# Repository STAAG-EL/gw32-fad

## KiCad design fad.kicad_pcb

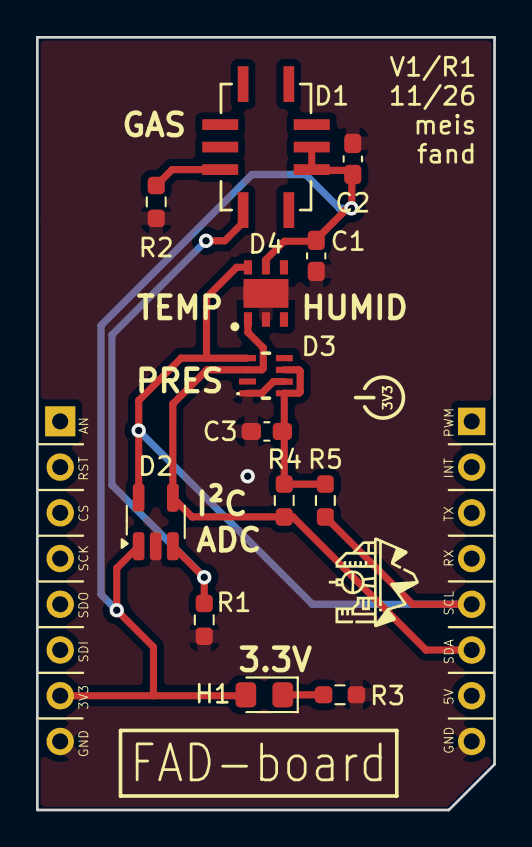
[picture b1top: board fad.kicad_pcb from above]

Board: 2 copper layers, 25.4 x 42.9 mm, 14 parts (0 on the bottom side), 7 nets.

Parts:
C1, C2, C3: 100n; C_0603_1608Metric_Pad1.08x0.95mm_HandSolder
D1: MICS-5524; MICS-SMD10
D2: MCP3221; SOT-23-5_HandSoldering
D3: DPS368
D4: HPP845E031R5; SON100P300X300X100-7N
H1: BU; LED_0805_2012Metric_Pad1.15x1.40mm_HandSolder
R1, R4, R5: 4k7; R_0603_1608Metric_Pad0.98x0.95mm_HandSolder
R2: 82R; R_0603_1608Metric_Pad0.98x0.95mm_HandSolder
R3: 1k; R_0603_1608Metric_Pad0.98x0.95mm_HandSolder
X1: MIKROBUS_MODULE_CONN

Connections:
+3V3: C1.1, C2.1, C3.1, D1.F (F/RH2), D1.G (G/RS2), D2.1 (V_{DD}), D3.6 (VDDIO), D3.8 (VDD), D4.5 (VDD), H1.2 (A), R4.1, R5.2, X1.P7
GND: C1.2, C2.2, C3.2, D2.2 (V_{SS}), D3.1 (GND_1), D3.7 (GND_2), D4.2 (GND), D4.7 (EP), R1.1, R2.1, R3.1, X1.P8, X1.P9
unnamed: D1.C (C/RH1), R2.2
unnamed: D1.D (D/RS1), D2.3 (A_{IN}), R1.2
unnamed: H1.1 (C), R3.2
SCL: D2.5 (SCL), D3.4 (SCK), D4.6 (SCK), R5.1, X1.P12
SDA: D2.4 (SDA), D3.3 (SDI), D4.1 (DATA), R4.2, X1.P11
